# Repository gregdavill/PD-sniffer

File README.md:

# PD-Sniffer

This project is based off the Twinkie, a Google designed PD sniffer/analyser. [link](https://www.chromium.org/chromium-os/developer-library/guides/hardware-schematics/twinkie/)

Unfortunately the original designers of the Twinkie designed the hardware with laptop like specifications. As a result the design features a 6L PCB with stacked micro-vias. This makes it expensive to manufacture.

This re-design aims to keep the board specifications within the scope of PCB prototyping services, so it is easier for hobbyists and other open-source contributors to create and build a unit.

## Hardware versions

### v0.1 (FreshTwinkie)
The initial version aims to remain pin compatible with the original design, so firmware can be re-used. The main MCU is swapped from a BGA package to a QFN, and a 4L board construction is used. As a result many BGA devices are still used, as these were un-changed from the original design.

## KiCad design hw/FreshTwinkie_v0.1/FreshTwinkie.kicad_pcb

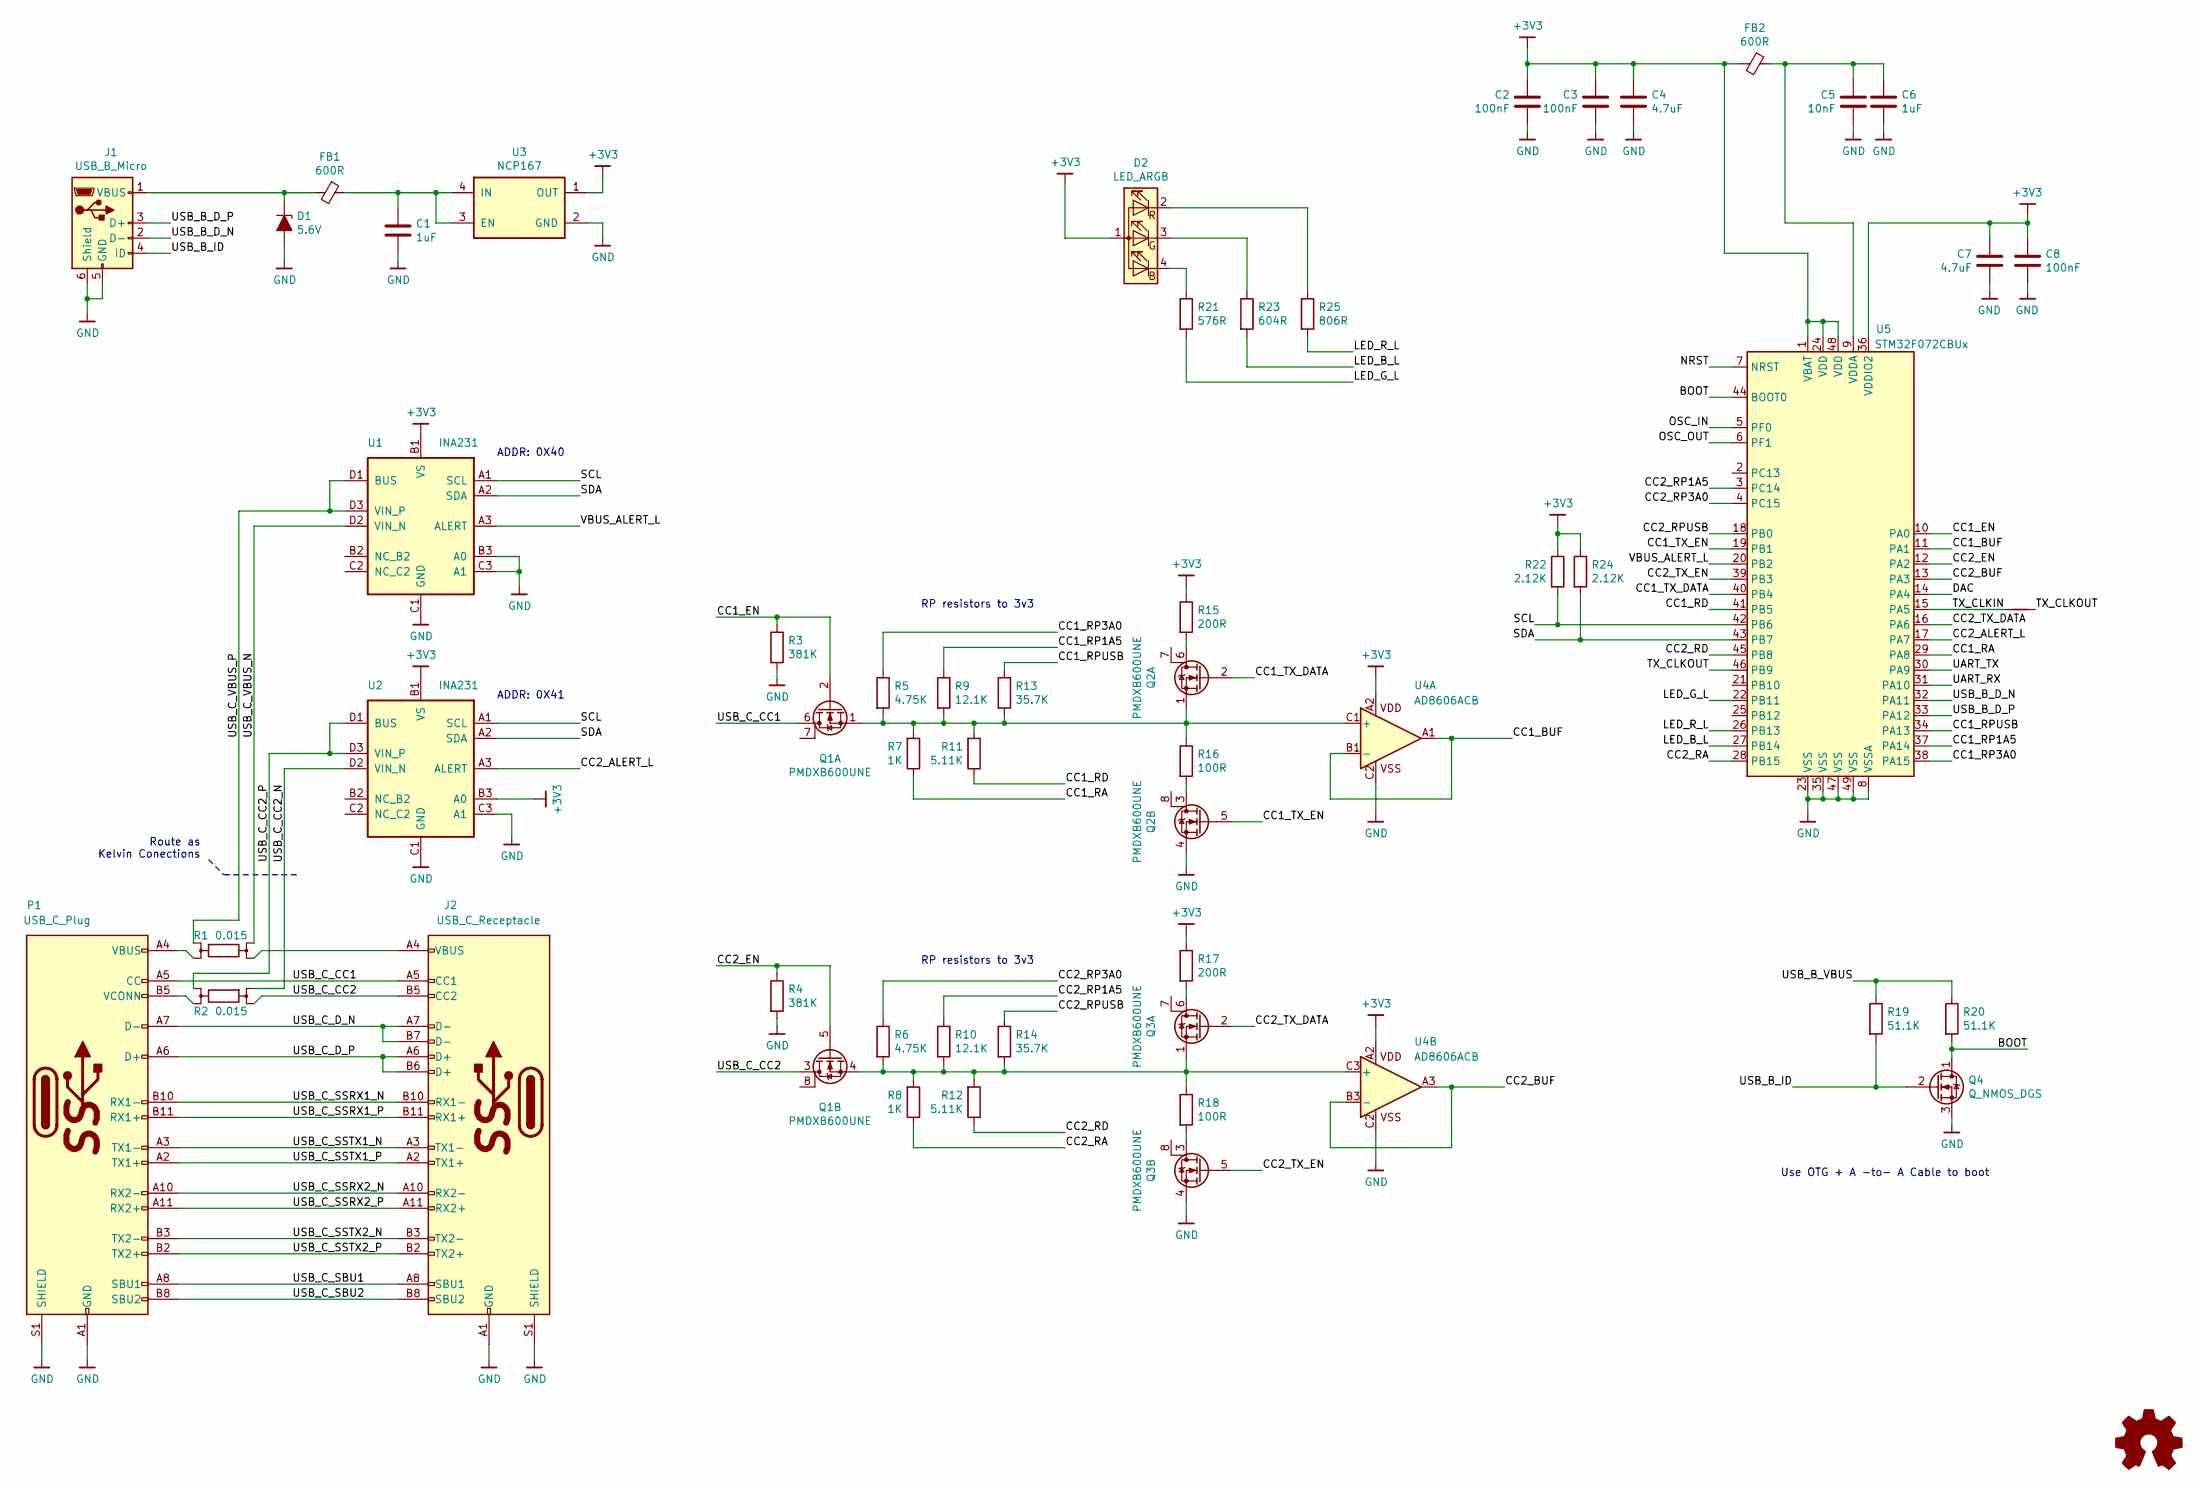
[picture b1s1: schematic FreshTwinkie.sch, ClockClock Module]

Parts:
C1, C6: 1uF; C_0402
C2, C3, C8: 100nF; C_0201
C4, C7: 4.7uF; C_0402
C5: 10nF; C_0201
D1: 5.6V; D_0402_1005Metric
D2: LED_ARGB; 0404LED_RGB
FB1, FB2: 600R; L_0402
J1: USB_B_Micro; USB_Micro-B_GCT_USB3076-30-A
J2: USB_C_Receptacle; USB_C_Receptacle_Amphenol_12401610E4-2A
NT1: Net-Tie_2; NetTie-2_SMD_Pad0.5mm
P1: USB_C_Plug; USB_C_Plug_Molex_105444
Q1, Q2, Q3: PMDXB600UNE; DFN1010B-6 (SOT1216)
Q4: Q_NMOS_DGS; MOSFET_1.0x0.6mm
R1, R2: 0.015; 4W_R_1206
R3, R4: 381K; R_0201
R5, R6: 4.75K; R_0201
R7, R8: 1K; R_0201
R9, R10: 12.1K; R_0201
R11, R12: 5.11K; R_0201
R13, R14: 35.7K; R_0201
R15, R17: 200R; R_0201
R16, R18: 100R; R_0201
R19, R20: 51.1K; R_0201
R21: 576R; R_0201
R22, R24: 2.12K; R_0201
R23: 604R; R_0201
R25: 806R; R_0201
U1, U2: INA231; DSBGA-12_1.56x1.39mm_Layout3x4_P0.4mm
U3: NCP167; X2SON_4_1.0x1.0mm
U4: AD8606ACB; WLCSP-8 3X3_0.5
U5: STM32F072CBUx; QFN-48-1EP_7x7mm_P0.5mm_EP5.6x5.6mm

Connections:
+3V3: C2.1, C3.1, C4.1, C7.1, C8.1, D2.1 (A), FB2.2, R15.1, R17.1, R22.1, R24.1, U1.B1 (VS), U2.B1 (VS), U2.B3 (A0), U3.1 (OUT), U4.A2, U5.1 (VBAT), U5.24 (VDD), U5.36 (VDDIO2), U5.48 (VDD)
/BOOT: Q4.1 (D), R20.2, U5.44 (BOOT0)
/CC1_BUF: U4.A1, U4.B1 (-), U5.11 (PA1)
/CC1_EN: Q1.2 (G), R3.1, U5.10 (PA0)
/CC1_RA: R7.1, U5.29 (PA8)
/CC1_RD: R11.1, U5.41 (PB5)
/CC1_RP1A5: R9.1, U5.37 (PA14)
/CC1_RP3A0: R5.1, U5.38 (PA15)
/CC1_RPUSB: R13.1, U5.34 (PA13)
/CC1_TX_DATA: Q2.2 (G), U5.40 (PB4)
/CC1_TX_EN: Q2.5 (G), U5.19 (PB1)
/CC2_ALERT_L: U2.A3 (ALERT), U5.17 (PA7)
/CC2_BUF: U4.A3, U4.B3 (-), U5.13 (PA3)
/CC2_EN: Q1.5 (G), R4.1, U5.12 (PA2)
/CC2_RA: R8.1, U5.28 (PB15)
/CC2_RD: R12.1, U5.45 (PB8)
/CC2_RP1A5: R10.1, U5.3 (PC14)
/CC2_RP3A0: R6.1, U5.4 (PC15)
/CC2_RPUSB: R14.1, U5.18 (PB0)
/CC2_TX_DATA: Q3.2 (G), U5.16 (PA6)
/CC2_TX_EN: Q3.5 (G), U5.39 (PB3)
/DAC: U5.14 (PA4)
/LED_B_L: R23.2, U5.27 (PB14)
/LED_G_L: R21.2, U5.22 (PB11)
/LED_R_L: R25.2, U5.26 (PB13)
/NRST: U5.7 (NRST)
/OSC_IN: U5.5 (PF0)
/OSC_OUT: U5.6 (PF1)
/SCL: R22.2, U1.A1 (SCL), U2.A1 (SCL), U5.42 (PB6)
/SDA: R24.2, U1.A2 (SDA), U2.A2 (SDA), U5.43 (PB7)
/TX_CLKIN: NT1.1, U5.15 (PA5)
/TX_CLKOUT: NT1.2, U5.46 (PB9)
/UART_RX: U5.31 (PA10)
/UART_TX: U5.30 (PA9)
/USB_B_D_N: J1.2 (D-), U5.32 (PA11)
/USB_B_D_P: J1.3 (D+), U5.33 (PA12)
/USB_B_ID: J1.4 (ID), Q4.2 (G), R19.2
/USB_B_VBUS: R19.1, R20.1
/USB_C_CC1: J2.A5 (CC1), P1.A5 (CC), Q1.6 (D)
/USB_C_CC2: J2.B5 (CC2), Q1.3 (D), R2.4
/USB_C_CC2_N: R2.2, U2.D2 (VIN_N)
/USB_C_CC2_P: R2.1, U2.D1 (BUS), U2.D3 (VIN_P)
/USB_C_D_N: J2.A7 (D-), J2.B7 (D-), P1.A7 (D-)
/USB_C_D_P: J2.A6 (D+), J2.B6 (D+), P1.A6 (D+)
/USB_C_SBU1: J2.A8 (SBU1), P1.A8 (SBU1)
/USB_C_SBU2: J2.B8 (SBU2), P1.B8 (SBU2)
/USB_C_SSRX1_N: J2.B10 (RX1-), P1.B10 (RX1-)
/USB_C_SSRX1_P: J2.B11 (RX1+), P1.B11 (RX1+)
/USB_C_SSRX2_N: J2.A10 (RX2-), P1.A10 (RX2-)
/USB_C_SSRX2_P: J2.A11 (RX2+), P1.A11 (RX2+)
/USB_C_SSTX1_N: J2.A3 (TX1-), P1.A3 (TX1-)
/USB_C_SSTX1_P: J2.A2 (TX1+), P1.A2 (TX1+)
/USB_C_SSTX2_N: J2.B3 (TX2-), P1.B3 (TX2-)
/USB_C_SSTX2_P: J2.B2 (TX2+), P1.B2 (TX2+)
/USB_C_VBUS_N: R1.1, U1.D2 (VIN_N)
/USB_C_VBUS_P: R1.2, U1.D1 (BUS), U1.D3 (VIN_P)
/VBUS_ALERT_L: U1.A3 (ALERT), U5.20 (PB2)
GND: C1.2, C2.2, C3.2, C4.2, C5.2, C6.2, C7.2, C8.2, D1.2 (A), J1.5 (GND), J1.6 (Shield), J2.A1 (GND), J2.A12 (GND), J2.B1 (GND), J2.B12 (GND), J2.S1 (SHIELD), P1.A1 (GND), P1.A12 (GND), P1.B1 (GND), P1.B12 (GND), P1.S1 (SHIELD), Q2.4 (S), Q3.4 (S), Q4.3 (S), R3.2, R4.2, U1.B3 (A0), U1.C1 (GND), U1.C3 (A1), U2.C1 (GND), U2.C3 (A1), U3.2 (GND), U4.C2, U5.8 (VSSA), U5.23 (VSS), U5.35 (VSS), U5.47 (VSS), U5.49 (VSS)
unnamed: C1.1, FB1.1, U3.3 (EN), U3.4 (IN)
unnamed: C5.1, C6.1, FB2.1, U5.9 (VDDA)
unnamed: D1.1 (K), FB1.2, J1.1 (VBUS)
unnamed: D2.2 (RK), R25.1
unnamed: D2.3 (GK), R23.1
unnamed: D2.4 (BK), R21.1
unnamed: J2.A4 (VBUS), J2.A9 (VBUS), J2.B4 (VBUS), J2.B9 (VBUS), R1.3
unnamed: P1.A4 (VBUS), P1.A9 (VBUS), P1.B4 (VBUS), P1.B9 (VBUS), R1.4
unnamed: P1.B5 (VCONN), R2.3
unnamed: Q1.1 (S), Q2.1 (S), R5.2, R7.2, R9.2, R11.2, R13.2, R16.1, U4.C1 (+)
unnamed: Q1.4 (S), Q3.1 (S), R6.2, R8.2, R10.2, R12.2, R14.2, R18.1, U4.C3 (+)
unnamed: Q2.3 (D), R16.2
unnamed: Q2.6 (D), R15.2
unnamed: Q3.3 (D), R18.2
unnamed: Q3.6 (D), R17.2

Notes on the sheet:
Route as Kelvin Conections
Use OTG + A -to- A Cable to boot
RP resistors to 3v3
ADDR: 0X41
ADDR: 0X40

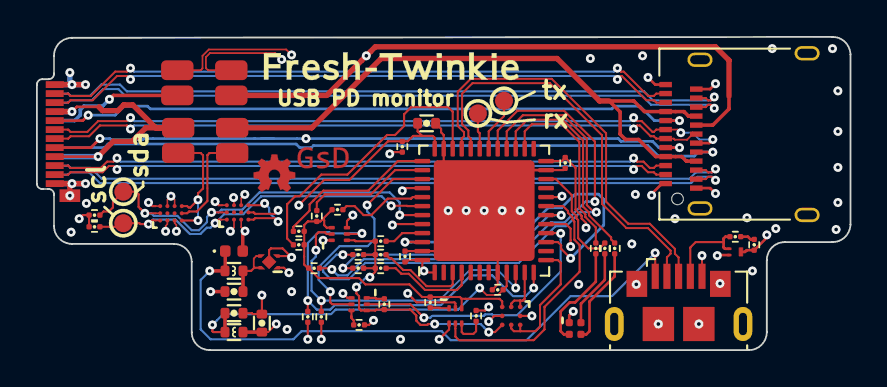
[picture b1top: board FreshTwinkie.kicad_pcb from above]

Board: 4 copper layers, 45.2 x 17.4 mm, 50 parts (1 on the bottom side), 67 nets.

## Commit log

2021-01-21 Add FreshTwinkie v0.1 hardware files
2021-01-21 Add README image
2023-06-09 Add 3d printable case
2025-05-31 fix: dead link to chromium.org's Twinkie
